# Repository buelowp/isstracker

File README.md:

# Use an opaque globe to show the position of the ISS using a laser
This project is going to project the ISS location on a globe showing current position continuously. The system uses a Particle Argon, one stepper motor for longitude rotation, and one servo motor for latitude rotation. It also uses a LOT of other parts listed in the BOM to make this work.

The goal is to provide a good looking device that is accurate and consistent. All of the motors and electronics must be hidden, and all parts must be independently moveable. So, the globe must be able to rotate without changing where the laser is pointing. The laser must work inside the globe independent of the base. The laser must also rotate 360 degrees longitude. The ISS does not go above or below ~60 degrees latitude, so a simple servo can be used for that.

A Particle project named isstracker

I found a similar project using an ESP8266 about 5 years ago and I was intrigued. So, I started hacking something up, but my requirements became much more complex than the original project. I wanted full rotation and to be able to *spin* the globe sitting on a base without changing where the location of the point showing the ISS.

It uses two independent sliprings which provide the ability to rotate the globe and the armature holding the laser without losing precision. It uses one 200 step NEMA stepper for longitude, and one 160 degree servo for the latitiude. The laser is from Sparkfun, but any laser that can be powered by 3 volts would work.

Pictures to follow

## Building it

Instructions to follow

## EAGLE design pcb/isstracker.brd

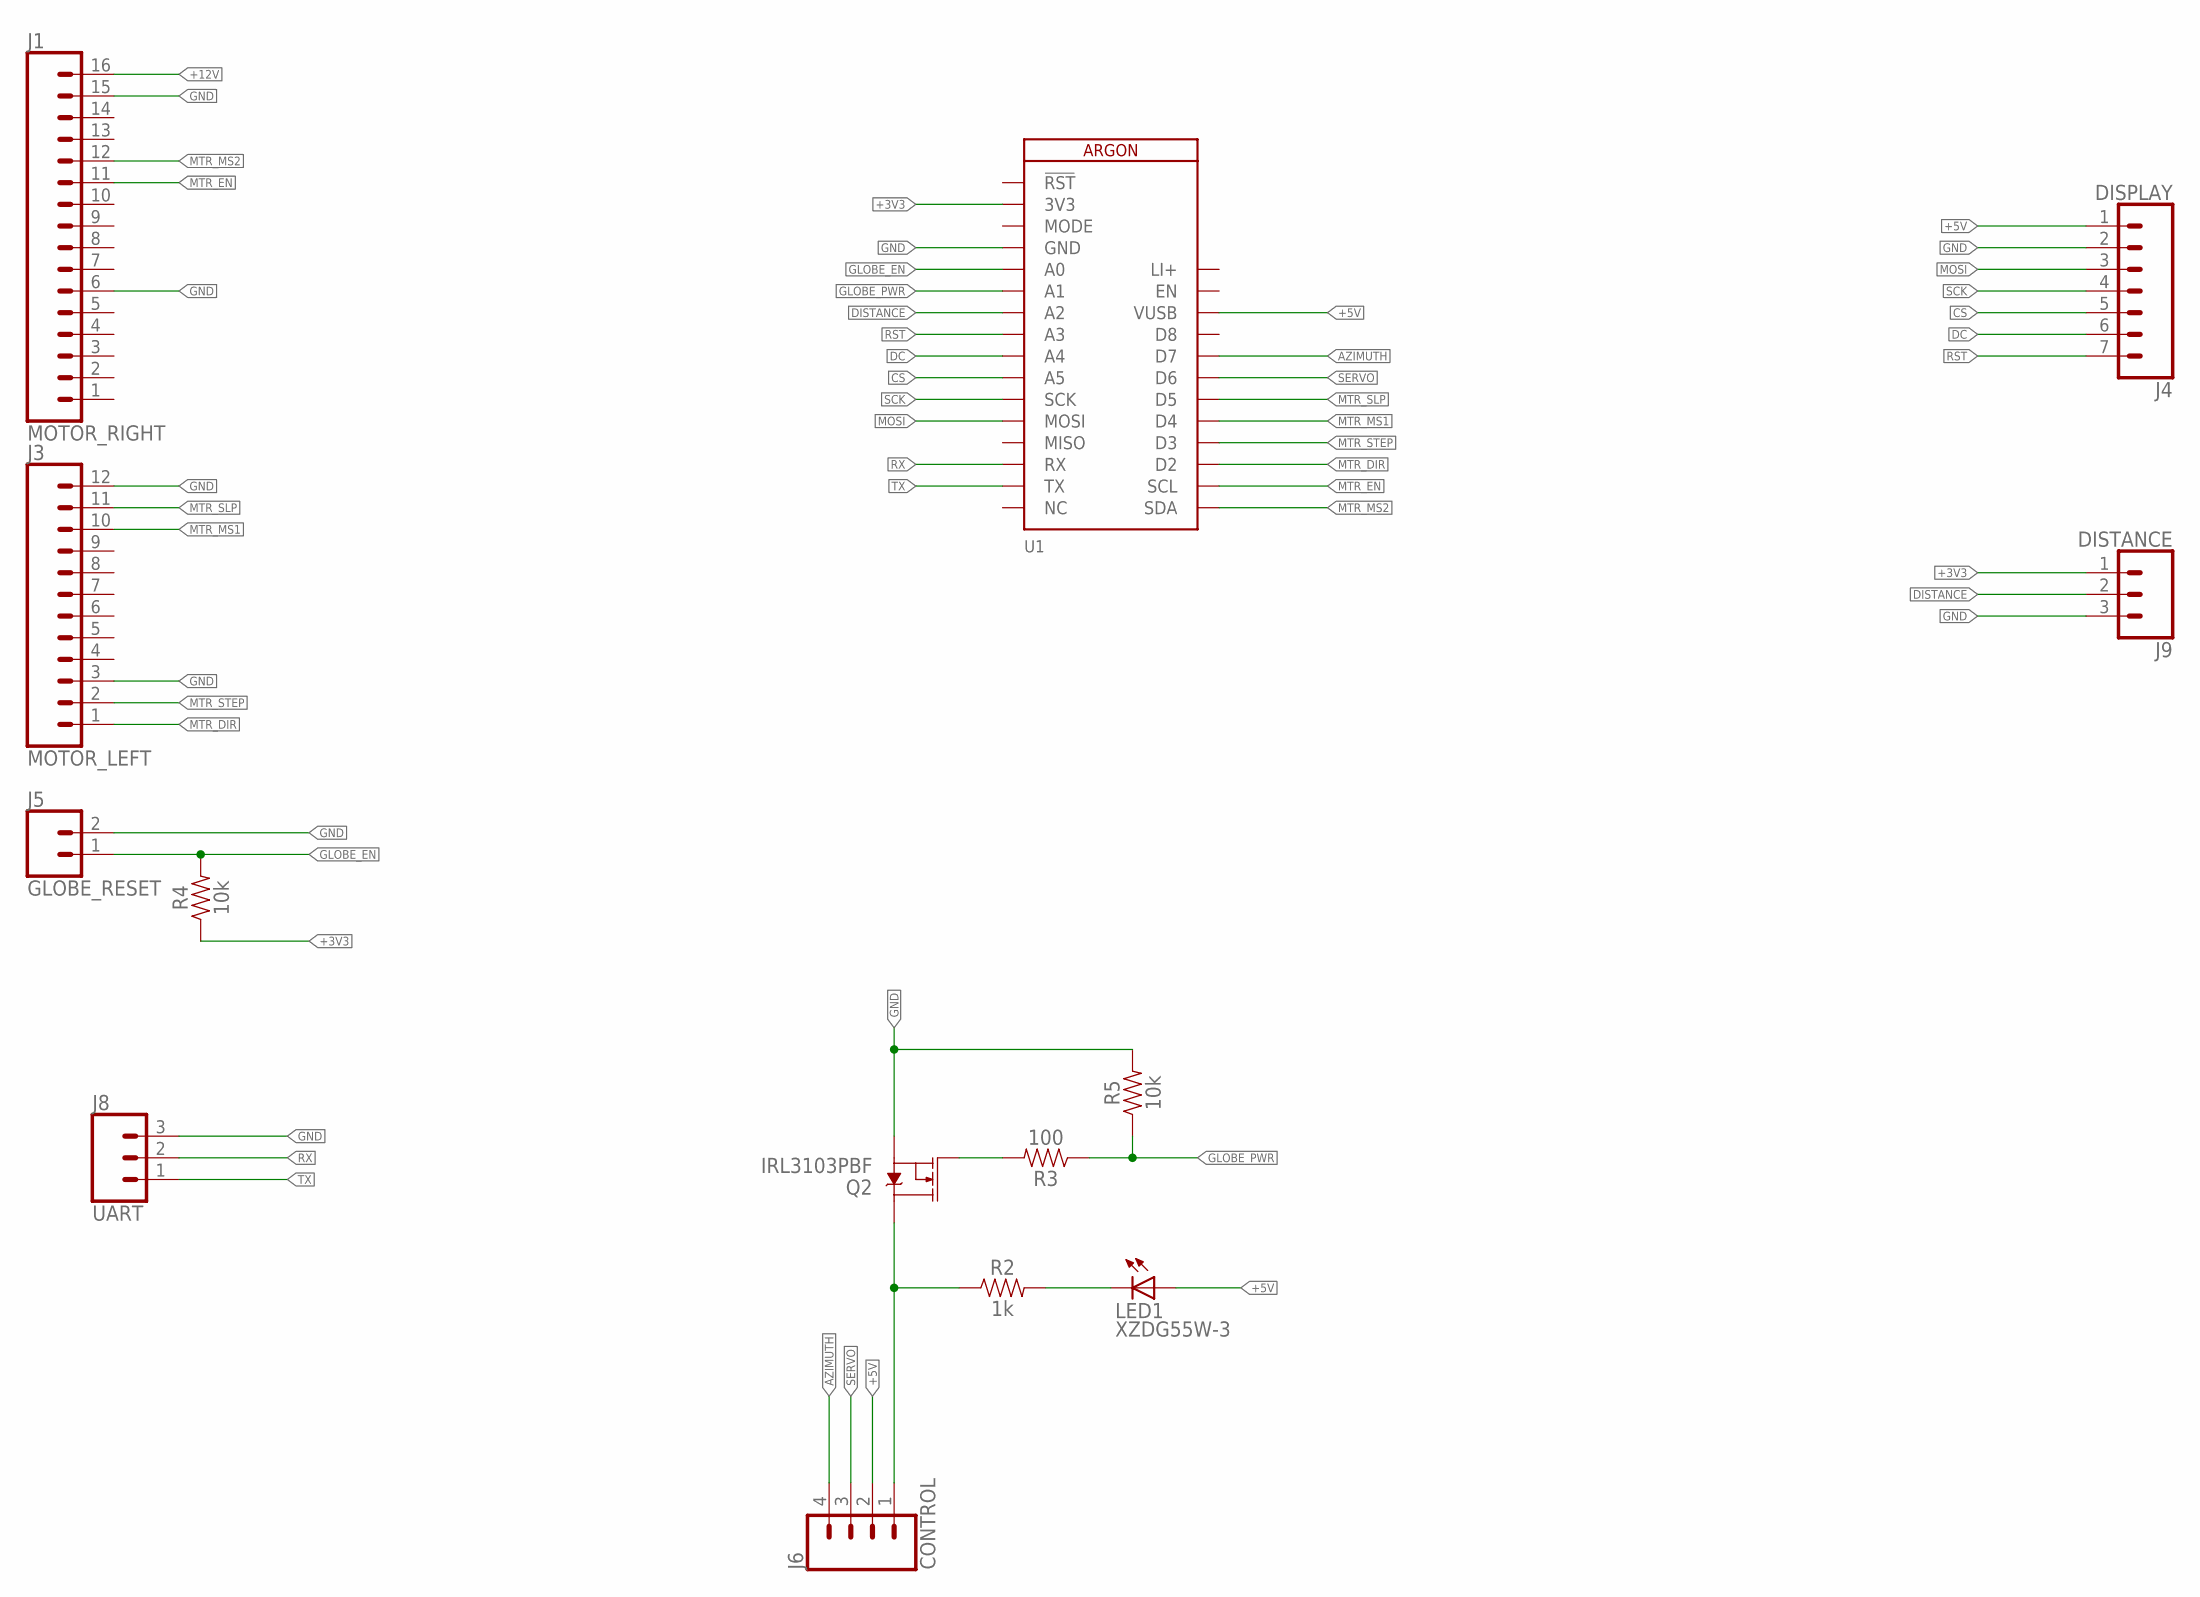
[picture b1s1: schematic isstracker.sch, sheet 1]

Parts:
J1: MOTOR_RIGHT; 1X16
J3: MOTOR_LEFT; 1X12
J4: DISPLAY; 1X07
J5: GLOBE_RESET; 1X02
J6: CONTROL; 1X04
J8: UART; 1X03
J9: DISTANCE; 1X03
LED1: XZDG55W-3; CHIPLED_1206
Q2: IRL3103PBF; TO220V
R2: 1k; 0805
R3: 100; 0805
R4, R5: 10k; 0805
U1: ARGON

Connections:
+3V3: J9.1, R4.1, U1.2 (3V3)
+5V: J4.1, J6.2, LED1.A, U1.26 (VUSB); also elsewhere on the board
+12V: J1.16; also elsewhere on the board
AZIMUTH: J6.4, U1.24 (D7)
CS: J4.5, U1.10 (A5)
DC: J4.6, U1.9 (A4)
DISTANCE: J9.2, U1.7 (A2)
GLOBE_EN: J5.1, R4.2, U1.5 (A0)
GLOBE_PWR: R3.1, R5.1, U1.6 (A1)
GND: J1.6, J1.15, J3.3, J3.12, J4.2, J5.2, J8.3, J9.3, Q2.3 (S), R5.2, U1.4 (GND); also elsewhere on the board
LI+: U1.28 (LI+)
MOSI: J4.3, U1.12 (MOSI)
MTR_DIR: J3.1, U1.19 (D2)
MTR_EN: J1.11, U1.18 (SCL)
MTR_MS1: J3.10, U1.21 (D4)
MTR_MS2: J1.12, U1.17 (SDA)
MTR_SLP: J3.11, U1.22 (D5)
MTR_STEP: J3.2, U1.20 (D3)
unnamed: Q2.1 (G), R3.2
unnamed: LED1.C, R2.2
unnamed: J6.1, Q2.2 (D), R2.1
RST: J4.7, U1.8 (A3)
RX: J8.2, U1.14 (RX)
SCK: J4.4, U1.11 (SCK)
SERVO: J6.3, U1.23 (D6)
TX: J8.1, U1.15 (TX)

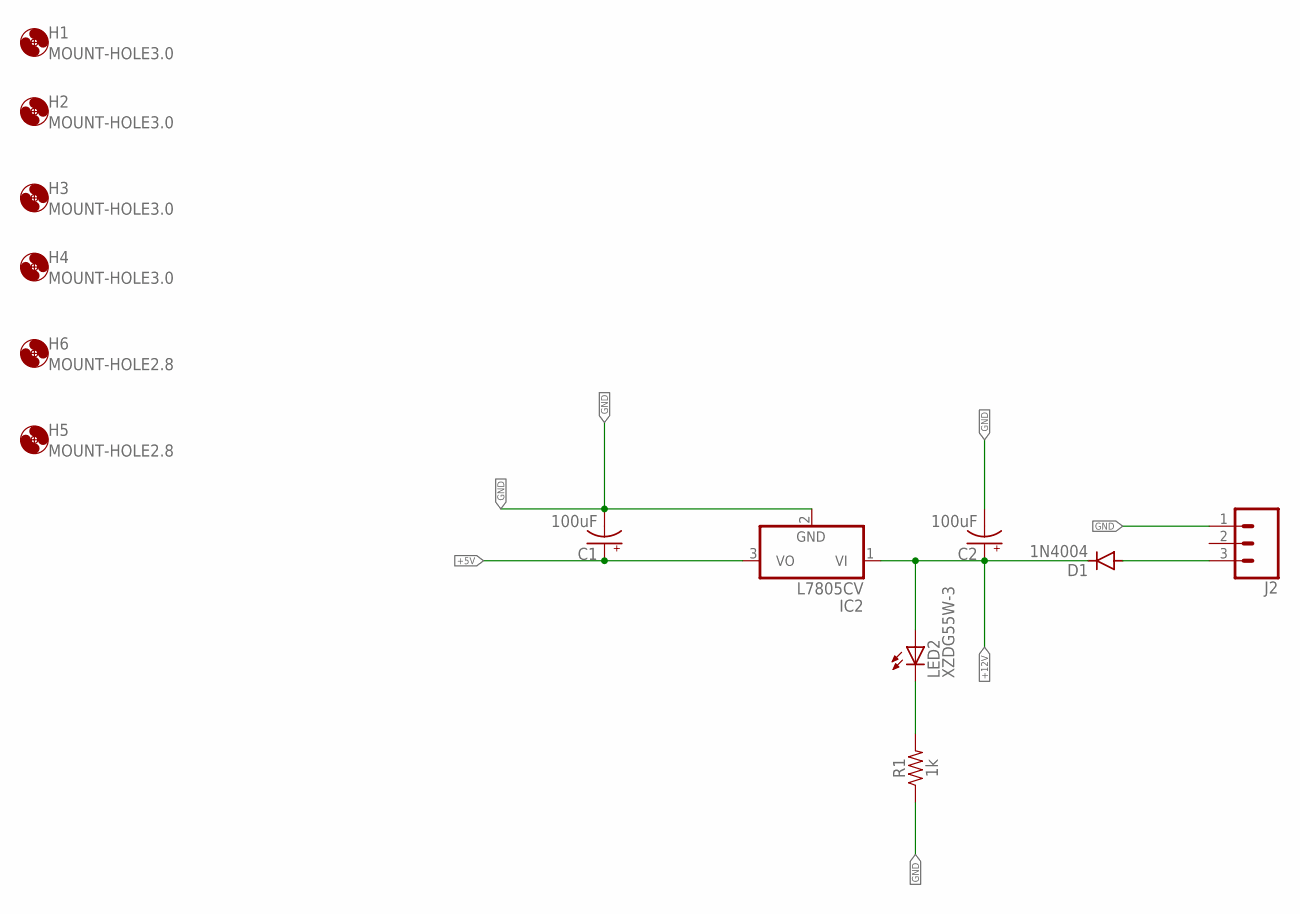
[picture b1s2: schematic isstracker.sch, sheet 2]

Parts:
C1, C2: 100uF; CPOL-RADIAL-2.5MM-6.5MM
D1: 1N4004; DO41-10
H1, H2, H3, H4: MOUNT-HOLE3.0; 3,0
H5, H6: MOUNT-HOLE2.8; 2,8
IC2: L7805CV; TO220V
J2: CONN_03LOCK_LONGPADS; 1X03_LOCK_LONGPADS
LED2: XZDG55W-3; CHIPLED_1206
R1: 1k; 0805

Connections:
+5V: C1.1 (+), IC2.3 (VO); also elsewhere on the board
+12V: C2.1 (+), D1.C, IC2.1 (VI), LED2.A; also elsewhere on the board
GND: C1.2 (-), C2.2 (-), IC2.2 (GND), J2.1, R1.1; also elsewhere on the board
unnamed: D1.A, J2.3
unnamed: LED2.C, R1.2

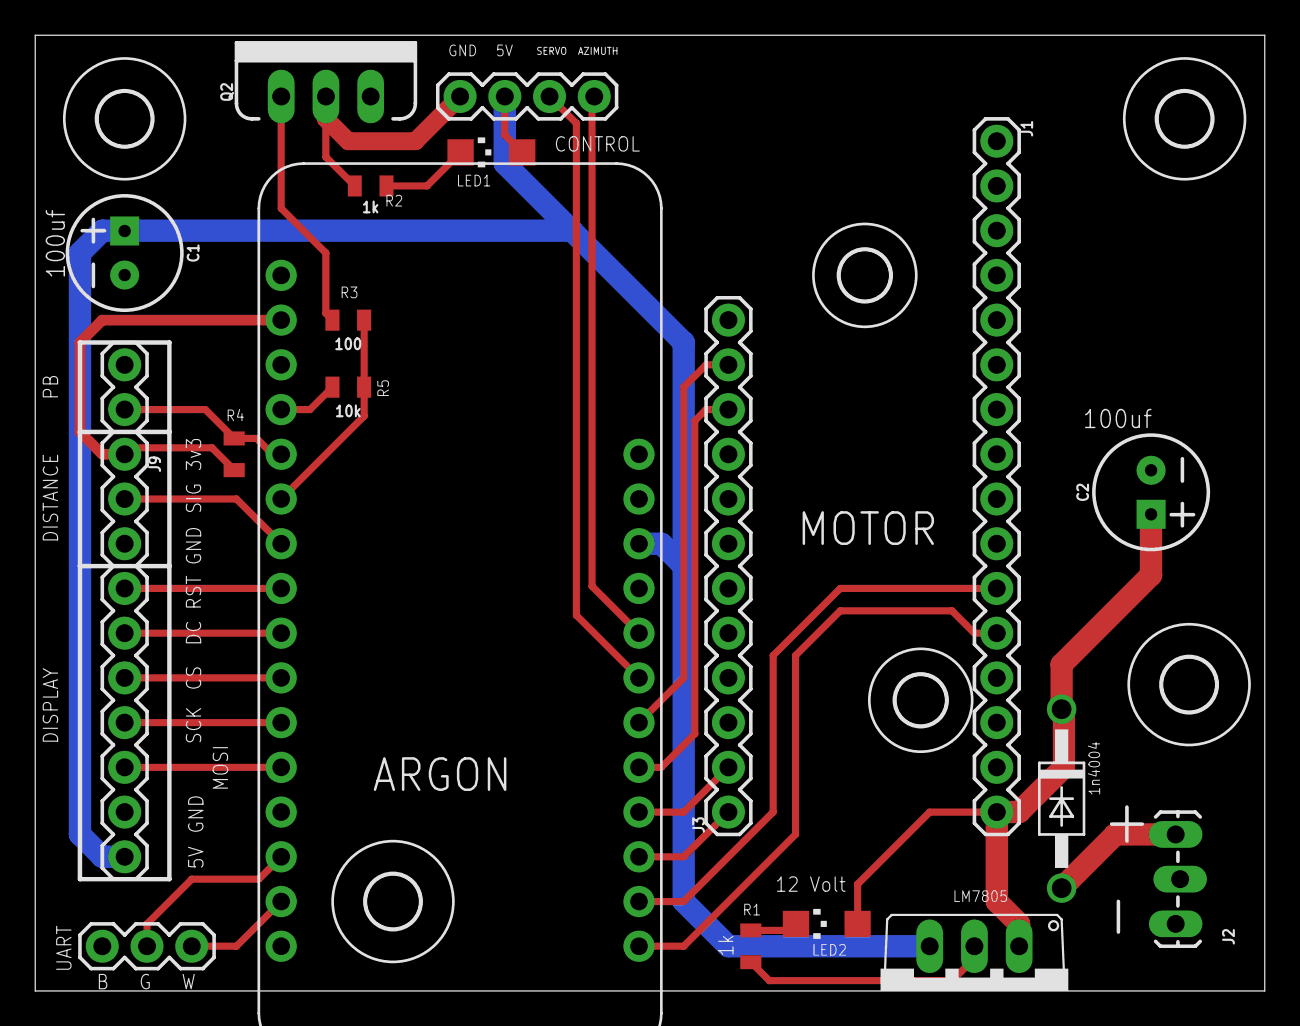
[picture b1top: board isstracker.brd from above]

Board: 2 copper layers, 69.8 x 54.3 mm, 27 parts (0 on the bottom side), 27 nets.

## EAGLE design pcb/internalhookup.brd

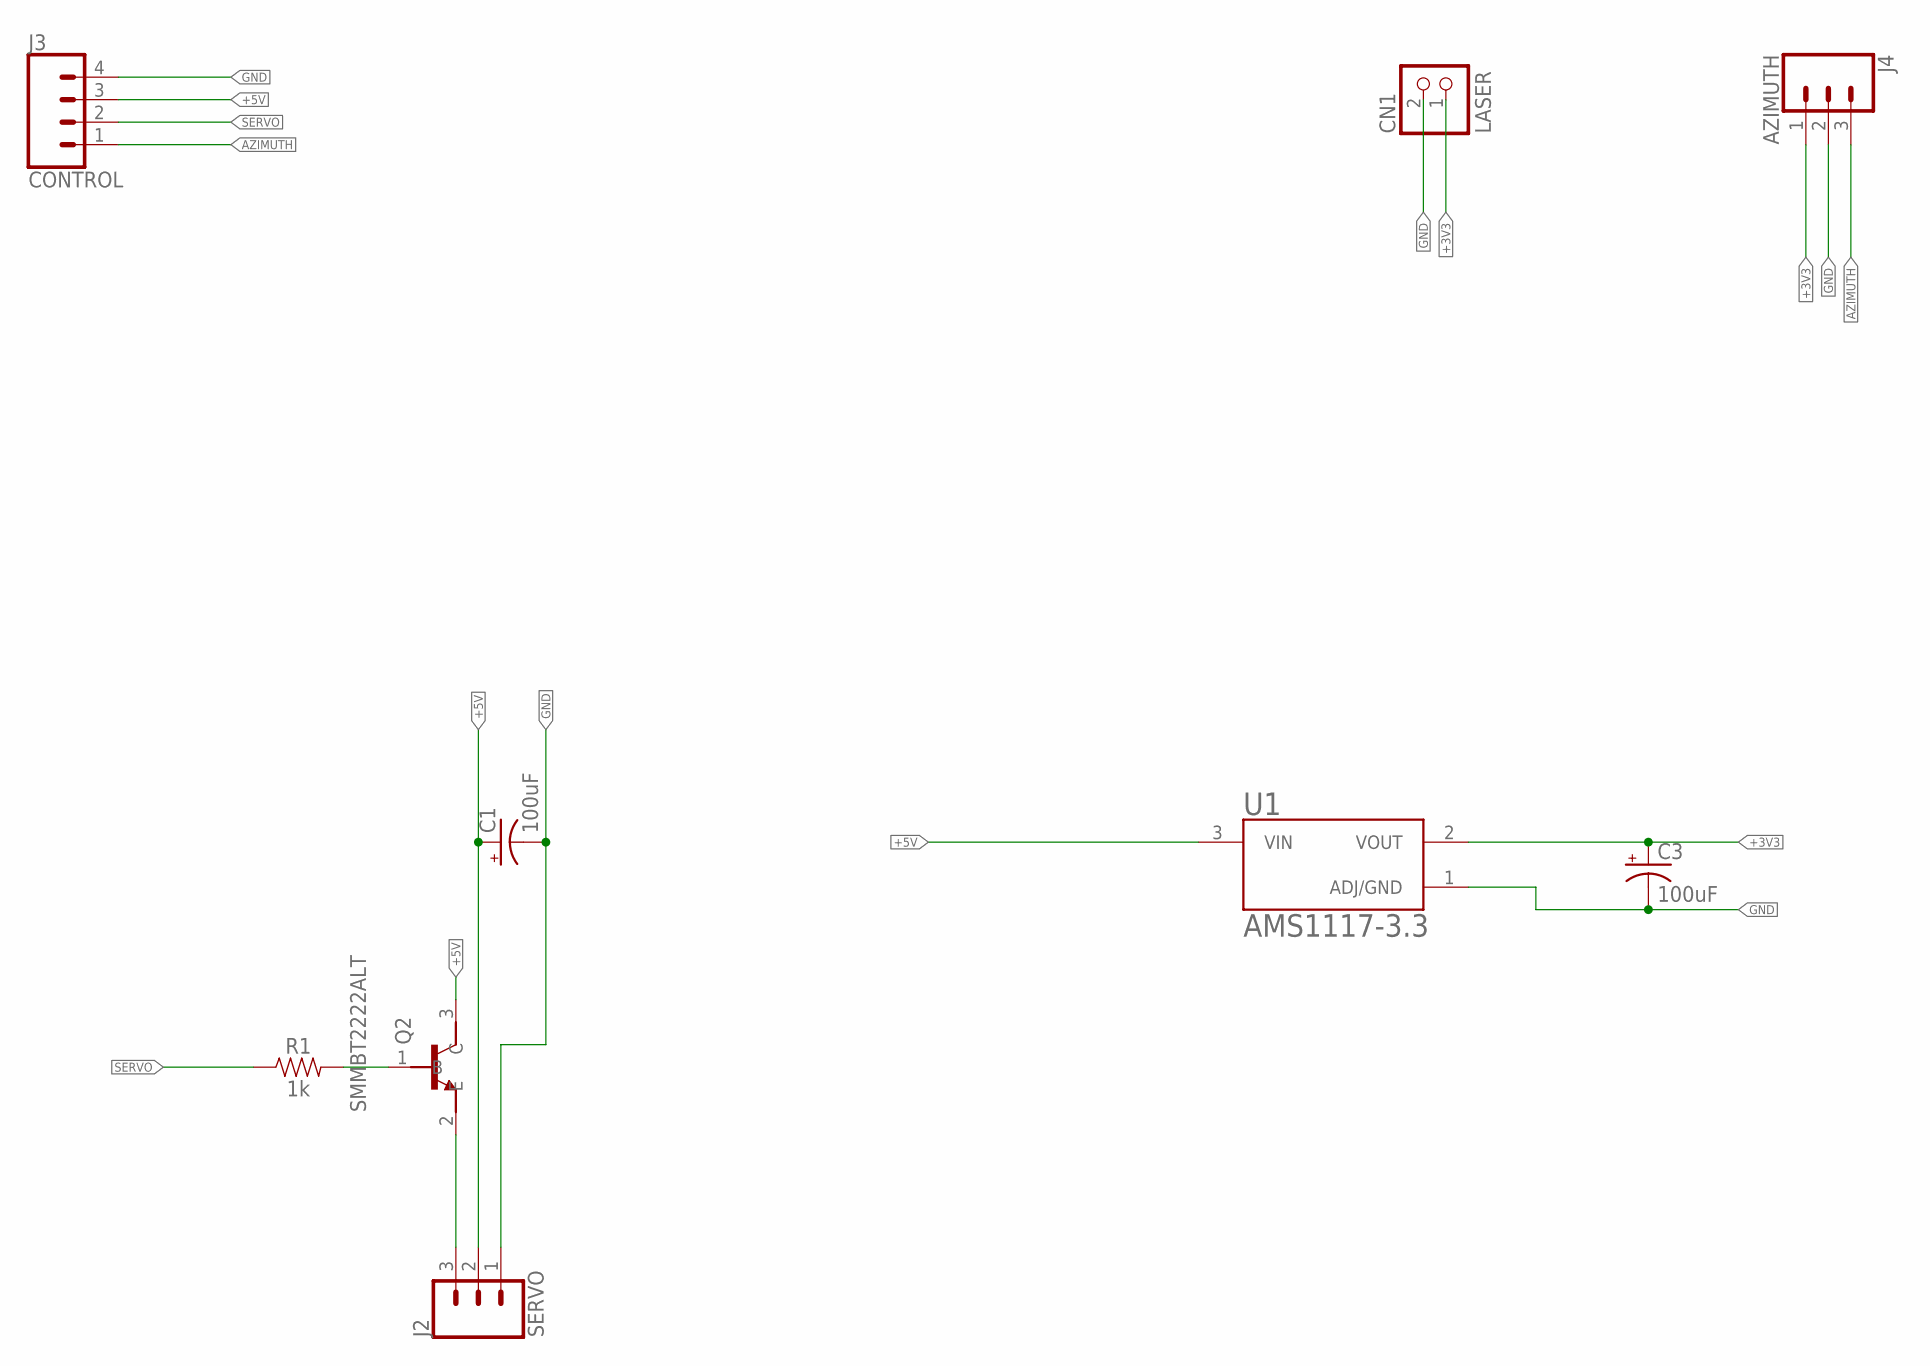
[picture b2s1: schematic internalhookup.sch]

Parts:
C1, C3: 100uF; CPOL-RADIAL-2.5MM-6.5MM
CN1: LASER; JST-PH-2-THM-RA
J2: SERVO; 1X03
J3: CONTROL; 1X04
J4: AZIMUTH; 1X03
Q2: SMMBT2222ALT; SOT95P240X120-3N
R1: 1k; 0805
U1: AMS1117-3.3; SOT229P700X180-4N

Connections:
+3V3: C3.1 (+), CN1.1 (2), J4.1, U1.2 (VOUT)
+5V: C1.1 (+), J2.2, J3.3, Q2.3 (C), U1.3 (VIN)
AZIMUTH: J3.1, J4.3
GND: C1.2 (-), C3.2 (-), CN1.2 (1), J2.1, J3.4, J4.2, U1.1 (ADJ/GND)
unnamed: Q2.1 (B), R1.2
unnamed: J2.3, Q2.2 (E)
SERVO: J3.2, R1.1

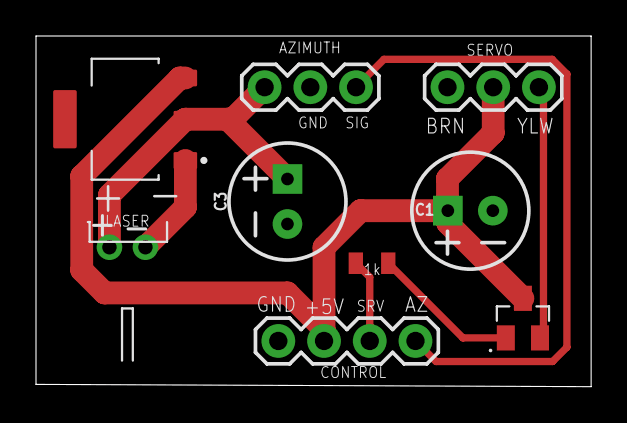
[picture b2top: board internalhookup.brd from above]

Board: 2 copper layers, 30.8 x 19.5 mm, 9 parts (0 on the bottom side), 7 nets.

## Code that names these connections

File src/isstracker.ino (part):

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#define CS                  A5
#define RST                 A3
#define DC                  A4
#define DISTANCE            A2
#define LASER_POWER         D2
#define MOTOR_ERR           D6
#define WIFI_ERR            D7
#define SERVO               D5
#define AZIMUTH             D3

// system_tick_t values as it's measured in millis
#define ONE_SECOND          1000
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    Log.info("%s: inclination offset is %d", __FUNCTION__, g_incOffset);
    display.printf("Servo offset: %d\n", g_incOffset);

    pinMode(mtr_ms1, OUTPUT);
    pinMode(mtr_ms2, OUTPUT);
    pinMode(mtr_en, OUTPUT);
    pinMode(mtr_step, OUTPUT);
    pinMode(mtr_dir, OUTPUT);
    pinMode(AZIMUTH, INPUT);
    pinMode(DISTANCE, INPUT);
    pinMode(GLOBE_POWER, OUTPUT);
    pinMode(GLOBE_EN, INPUT);
 
    g_lastResetReason = System.resetReason();

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
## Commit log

2020-05-09 Fixed a bug with latitude calculations
2020-05-09 Fixes
    * Fixed a rounding problem
    * Changed a variable name to be more explicit
2021-01-22 Tracker version 45:
    * Cleaning up prints to the display
    * Migrating back to the git src, it's been on it's own for a while
2021-01-22 Updating repo with the non source code portions
2021-01-22 Readme updates
2021-01-22 Fixing PCB to use the new IR sensor instead.
2021-01-24 Version 47:
    * Only wake motor from sleep IFF we are going to move the motor
    * Clean up some extra logging
    * Add LED controls for the globe lighting
    * This includes the first PCB sent out for production at OSHPark
2021-02-06 Version 48
    * Added some colors and made it possible to cycle them on a timer
    * Fixed a display bug
2021-02-07 Updating to the latest PCB to fix breaking issues
    * Fixed capacitor sets for both boards to be larger and polarized on the
    LDO's
    * Fixed left track for motor board as it was 1 pin too short
    * Switched from Declination to Azimuth
    * Moved Azimuth signaling to the internal board to allow for movement
    * Removed resistors on 5V LED signal buffer
2021-02-08 Adding laser control
    * Hookup an NPN to be able to turn the laser on/off via A0
2021-02-09 Adding a duty cycle switch for a Laser
    * Currently unused, the laser I chose does it's own duty cycle, but
    for lasers that can't be on all the time, this will help.
2021-02-14 Lots of changes
    * Dropped LED's and LASER control
    * Renamed DECLINATION to AZIMUTH
    * Moved AZIMUTH control hookup into the globe (it needs to spin freely)
    I couldn't make the LED's fit and shine without casting shadows inside
    the globe. Plus, there wasn't much room, and it required more wires to
    make work. No a critical problem, but the challenges outweighed the
2021-02-17 PCB fixups
    * Bumped PCB revisions
    * Layout changes and some silk screen updates
    * No functionality changes
2021-02-23 Fixups
    * Add the ability to turn the power to the globe on and off via a MOSFET
    * Clean up some of the code
2021-02-23 More fixups
    * Migrate from declination to azimuth
    * Make the globe timeout independent of the display
2021-02-24 More fixups
    * Make the globe power control a toggle, the laser may be more robust
    than I assumed
2021-02-24 Adding a gitignore
2021-02-24 Hookup board revision to 1.6
    * Added a cap in front of the servo as the line to get the 5V is long
    and may not be totally reliable under stress
2021-03-04 Updating to build 53
    * Create a board rev define as I'm testing with an older board. It
    works, but isn't correct
    * Add N/S/E/W to the display to make it more clear where the ISS is
2021-03-06 Layout tweaks
    * Swap pth for smd LED's
    * Move globe power pin to new location
    * Add support hole for motor board if attached via headers
    * Layout fixes for globe with new 4 pin setup
2021-03-06 Control board version 1.7
    * Added a pushbutton to turn the globe back on
    * Began to put globe power control back into app
2021-03-06 Updating to version 54
    * This cleans up globe power control a lot
    * Adds a lot comments to help undestanding
    * Untested as the unit is still down until I update the boards
2021-03-06 Bump control board revision
    * Move pins around for display, motion, and pushbutton
    * Add pushbutton
2021-03-06 Update to version 1.9
    * Fix the FET, it wasn't right
    * New FET in the BOM
    * Put FET on low side and add pulldown on gate
2021-03-06 Adding BOM's
    * New BOM's for tracking components
2021-03-06 Updating LED BOM entry
2021-03-27 Fixes
    * Add globe power using a MOSFET so the laser can be turned on/off
    * Update both board layouts to accomodate new power scheme
    * Fix some component positions in layout
    * Migrate to screw terminals for power on board
2024-05-26 New PCB work
2024-05-26 Migrating to new version 2 of the model
2024-05-26 Added control for an LED for internal illumination
2024-05-26 Updating to add internal globe LED control
2024-08-17 Last updates using the ESP32, moving back to the Photon2
2024-08-17 Migrating from the ESP32 to the Photon2
    * Should make some operations easier

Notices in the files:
parts and their libraries:
SparkFun-Capacitors: Licensing: Creative Commons ShareAlike 4.0 International - https://creativecommons.org/licenses/by-sa/4.0
Particle-Devices: Licensing: Designed by Particle.
